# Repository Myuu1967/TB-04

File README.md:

# TB-04

自作 4bit CPU **TB-04** のプロジェクトリポジトリです。
TD4 ライクなアーキテクチャをベースに、ALU とデコーダを ROM で実装した独自設計の 4bit CPU です。
データ幅は 4bit のまま、世代ごとにアドレス空間を広げています。

TB-04 ver2 の実機。左は演算板（上）と制御板（下）を重ねたもの、右は IF 板、右端はクロック供給ユニット clock4096。

回路図・PCB（KiCAD）とプログラム・ツール類を、世代ごとのディレクトリにまとめています。回路図は KiCAD がなくても見られるよう PDF も置いています（各 README からリンク）。

## 世代

| 世代 | アドレス | 状態 | 主な特徴 | ディレクトリ |
|---|---|---|---|---|
| **ver1** | 4bit（16語） | 完成（2026-06） | 16命令・レジスタ R0〜R3・基板1枚 | [`ver1/`](ver1/) |
| **ver2** | 8bit（256語） | 完成（2026-10） | 2語命令・34命令・レジスタ R0〜R7・RAM とスタック・基板3枚・7セグ表示17台 | [`ver2/`](ver2/) |
| ver3 | 12bit（予定） | 構想中 | ポインタ・間接アドレッシング | — |

いずれも 1命令＝4クロック（ディレイスロットなし）で動きます。
各世代の仕様・ファイル構成・使い方は、それぞれのディレクトリの README を参照してください。

## 周辺機器

周辺ユニットは [`peripherals/`](peripherals/) に置いています。7segIF は ver1・ver2 のどちらでも使え、clock4096 は ver2 用です。

| ユニット | 内容 |
|---|---|
| [`7segIF`](peripherals/7segIF/) | 4bit を `0`〜`F` の7セグメントで表示するユニット（CH32V003）。ver2 では17台を使用 |
| [`clock4096`](peripherals/clock4096/) | ver2 用のクロック供給ユニット（RC 発振 4096Hz ＋ 分周、ロータリースイッチで周波数を選択）。ユニバーサル基板で製作・回路図（KiCAD・PDF）を公開 |

## ディレクトリ構成

```
ver1/         アドレス 4bit 版（回路図・PCB・アセンブラ・シミュレータ・サンプルプログラム・Pico 簡易ロジックアナライザ）
ver2/         アドレス 8bit 版（回路図・PCB・シミュレータ・ROM 生成ツール・高速ロジックアナライザ）
peripherals/  周辺ユニット（7segIF＝ver1・ver2 共通／clock4096＝ver2 用）
```

KiCAD のバージョンは、ver1 が 9.0（ロジックアナライザのみ 10.0）、ver2・7segIF・clock4096 が 10.0 です。

## 資料

- 展示会の配布資料「これまでに製作した自作CPUについてのまとめ」（2026-08-08・PDF）: <https://drive.google.com/file/d/16cySft4IG1u6tpTtqwmJSpbO6KQHhh4Z/view?usp=drive_link>
  CPU のしくみの解説と、TB-01（1bit）・TB-02（2bit）・TD4・TB-04 ver1 の構成と命令表をまとめたものです。

## ライセンス

[MIT License](LICENSE)（回路図・PCB・プログラム・ドキュメントを含む）。
ただし 7segIF の回路図・基板（`peripherals/7segIF/hardware/`）は、CC BY-SA 4.0 の作品をもとにしているため CC BY-SA 4.0 です（[`peripherals/7segIF/LICENSE`](peripherals/7segIF/LICENSE)）。

## 関連記事

ver1
- 設計編「【TB-04】4bitCPUの設計」: <https://tanuki-bayashin.hatenablog.com/entry/2026/05/27/140048>
- 完成編「【TB-04】4bitCPUの完成（アドレス4bitバージョン）」: <https://tanuki-bayashin.hatenablog.com/entry/2026/06/20/164917>
- ソースコード編「【TB-04】4bitCPUのソースコード編（シリーズ完結）」: <https://tanuki-bayashin.hatenablog.com/entry/2026/06/25/220134>
- ロジックアナライザー編「ラズベリーパイPicoによる簡易ロジックアナライザー」: <https://tanuki-bayashin.hatenablog.com/entry/2026/06/28/074330>

ver2
- 設計編「【TB-04】4bitCPUの設計（addr 8bit ver）」: <https://tanuki-bayashin.hatenablog.com/entry/2026/11/03/164404>
- 回路図とPCB設計編「【TB-04】4bitCPUの回路図とPCB設計(addr 8bit ver)」: <https://tanuki-bayashin.hatenablog.com/entry/2026/11/05/082909>
- 完成編「【TB-04】4bitCPUの完成（addr 8bit ver）」: <https://tanuki-bayashin.hatenablog.com/entry/2026/11/07/110004>
- デモ動画: <https://www.youtube.com/watch?v=xa86bRDYqcg>

周辺機器
- 「【TB-04用】7SEG表示装置（16進）の製作」: <https://tanuki-bayashin.hatenablog.com/entry/2026/08/18/172152>

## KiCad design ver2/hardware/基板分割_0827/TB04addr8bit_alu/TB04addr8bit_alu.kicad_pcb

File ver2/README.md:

# TB-04 ver2（アドレス 8bit 版）

TB-04 の2世代目です。データは 4bit のまま、アドレスを 8bit（256語）に広げ、RAM とスタックを加えました。
12bit アドレスの ver3 へ向けた通過点として作り、2026年10月にテストプログラムで全命令の動作を確認しました。
リポジトリ全体の説明は [トップの README](../README.md) を参照してください。

左は演算板（上）と制御板（下）を重ねたもの、右は IF 板、右端はクロック供給ユニット [`clock4096`](../peripherals/clock4096/)。

## アーキテクチャ

| 項目 | 仕様 |
|---|---|
| データ幅 | 4bit |
| アドレス幅 | 8bit（256語） |
| 命令形式 | 固定2語（2バイト）。1語目の上位ニブルが opcode、`E`/`F` は 8bit opcode へのプレフィックス |
| 命令数 | 34命令（ロード/ストア・PUSH/POP・CALL/RET・条件分岐4種・シフト/ローテートなど） |
| 汎用レジスタ | R0〜R7 |
| フラグ | C（キャリー）、Z（ゼロ）。書き込む命令だけが更新する（クロックゲート方式） |
| ALU | ROM 実装（28C256・入力 13bit・16演算） |
| デコーダ | ROM 実装（28C256 × 3） |
| プログラム ROM | 28C256（ZIF ソケット） |
| RAM・スタック | 6116 1個を共用。スタックは8段（SP は 3bit） |
| 制御タイミング | 4フェーズ（FCH1 → FCH2 → DCR → EXE）、1命令＝4クロック |
| 表示 | 7セグメント表示ユニット [7segIF](../peripherals/7segIF/) を17台直挿し（命令・MD・PC・OUT・IN など）＋ LED |

### メモリマップ

| アドレス | 用途 |
|---|---|
| `0x00`〜`0xBF` | プログラム ROM（192語＝96命令） |
| `0xC0`〜`0xEF` | RAM（データ 4bit） |
| `0xF0`〜`0xF7` | スタック（戻り番地 8bit） |
| `0xF8`〜`0xFB` | IN ポート 0〜3 |
| `0xFC`〜`0xFF` | OUT ポート 0〜3 |

## ブロック図

（PNG 版: [`tb04_ver2_block.png`](tb04_ver2_block.png)。図は `tools/gen_block_diagram.py` で生成）

### ブロックと主な IC

| 基板 | ブロック | 主な IC |
|---|---|---|
| IF 板 | クロック・リセット（水晶は不使用・外付け clock4096 からクロックを入れる） | 74HC14 ＋ clock4096（74HC04・4040） |
| IF 板 | IN ポート ×4 | 74HC244 ×4 |
| IF 板 | OUT ポート ×4 | 74HC377 ×4 |
| 制御板 | 位相発生（FCH1 / FCH2 / DCR / EXE） | 74HC161・74HC238 |
| 制御板 | 命令 ROM（ZIF・16バンク） | 28C256 |
| 制御板 | 命令レジスタ（byte1・byte2） | 74HC273 ×2 |
| 制御板 | デコーダ ROM ＋ 制御ラッチ | 28C256 ×2・74HC273 ×2 |
| 制御板 | PC ＋ 分岐先 MUX | 74HC161 ×2・74HC157 ×2 |
| 制御板 | SP（3bit） | 74HC193 |
| 制御板 | アドレス源の選択（mAddr / PC / SP / I-O）と IN・OUT ポートの選択 | 74HC244 ×4・74HC138・74HC157・74HC139 |
| 制御板 | 領域デコード・ゲート群 | 74HC08 ×2・74HC00 ×2・74HCT10・74HC32・74AHC04 |
| 制御板 | RAM ＋ スタック | 6116 |
| 制御板 | Y ラッチ・Y ドライバ（MD への書き出し） | 74HC273・74HC244 ×2 |
| 制御板 | Ri アドレス選択 | 74HC157 |
| 演算板 | レジスタ R0〜R7（書込先の選択を含む） | 74HC161 ×8・74HC138 |
| 演算板 | 読出し MUX（a ポート・b ポート） | 74HC253 ×8 |
| 演算板 | ALU 入力 MUX（a・b） | 74HC253 ×4 |
| 演算板 | ALU ROM | 28C256 |
| 演算板 | フラグ C / Z | 74HC74 |
| 演算板 | デコーダ ROM（ALU 用）＋ ラッチ | 28C256・74HC273 |

IC 68個の型式ごとの説明と、参照番号ごとの使い方は [`IC_LIST.md`](IC_LIST.md) にまとめています。

## 命令セット

1命令＝2語（byte1・byte2）。byte1 の上位ニブルが opcode で、`1110`（E系）・`1111`（F系）のときは下位ニブルまで含めた 8bit が opcode になります。
ビット配置の記号は `iii`=Ri、`jjj`=Rj、`mmmm`=即値、`aaaa aaaa`=番地、`pp`=ポート番号。

| 群 | 命令 | オペランド | byte1 | byte2 | 動作 | Z | C | ALU |
|---|---|---|---|---|---|:-:|:-:|---|
| 単独ニブル | NOP | - | `0000 0000` | `0000 0000` | 何もしない | - | - | NOP |
| 単独ニブル | MOV | Ri,Rj | `0001 0000` | `0iii 0jjj` | Ri←Rj | - | - | PASS_B |
| 単独ニブル | MOVI | Ri,Im4 | `0010 mmmm` | `0iii 0000` | Ri←Im4 | - | - | PASS_A |
| 単独ニブル | LD | Ri,[Im8] | `0011 0iii` | `aaaa aaaa` | Ri←MEM[Im8] | - | - | PASS_B |
| 単独ニブル | ST | [Im8],Ri | `0100 0iii` | `aaaa aaaa` | MEM[Im8]←Ri | - | - | PASS_A |
| 単独ニブル | STI | [Im8],Im4 | `0101 mmmm` | `aaaa aaaa` | MEM[Im8]←Im4 | - | - | PASS_A |
| 単独ニブル | （予約） | - | `0110/0111/1000` | — | ver3（12bitアドレス化）拡張用に温存（3枠） | - | - | - |
| E系 | JMP | Addr | `1110 0000` | `aaaa aaaa` | PC←Addr | - | - | - |
| E系 | JC | Addr | `1110 0001` | `aaaa aaaa` | C==1でPC←Addr | - | - | - |
| E系 | JNC | Addr | `1110 0010` | `aaaa aaaa` | C==0でPC←Addr | - | - | - |
| E系 | JZ | Addr | `1110 0011` | `aaaa aaaa` | Z==1でPC←Addr | - | - | - |
| E系 | JNZ | Addr | `1110 0100` | `aaaa aaaa` | Z==0でPC←Addr | - | - | - |
| E系 | CALL | Addr | `1110 0101` | `aaaa aaaa` | MEM[SP]←PC; PC←Addr; SP-- | - | - | - |
| E系 | RET | - | `1110 0110` | `0000 0000` | SP++; PC←MEM[SP] | - | - | - |
| 擬似 | HALT | - | — | — | PC←自番地（JMP $ に展開）。opcode 1110 0111 は予約 | - | - | - |
| E系 | PUSH | Ri | `1110 1000` | `0iii 0000` | MEM[SP]←Ri; SP-- | - | - | PASS_A |
| E系 | POP | Ri | `1110 1001` | `0iii 0000` | SP++; Ri←MEM[SP] | - | - | PASS_B |
| E系 | IN | Ri,port | `1110 1010` | `0iii 00pp` | Ri←IN[port] | ○ | - | PASS_B |
| E系 | OUT | port,Ri | `1110 1011` | `0iii 00pp` | OUT[port]←Ri | - | - | PASS_A |
| E系 | OUTI | port,Im4 | `1110 1100` | `00pp mmmm` | OUT[port]←Im4 | - | - | PASS_A |
| F系 | CP | Ri,Rj | `1111 0000` | `0iii 0jjj` | Ri−Rj（フラグのみ） | ○ | ○ | SUB |
| F系 | AND | Ri,Rj | `1111 0001` | `0iii 0jjj` | Ri←Ri&Rj | ○ | - | AND |
| F系 | OR | Ri,Rj | `1111 0010` | `0iii 0jjj` | Ri←Ri\|Rj | ○ | - | OR |
| F系 | XOR | Ri,Rj | `1111 0011` | `0iii 0jjj` | Ri←Ri^Rj | ○ | - | XOR |
| F系 | NOT | Ri | `1111 0100` | `0iii 0000` | Ri←!Ri | ○ | - | NOT |
| F系 | SHL | Ri | `1111 0101` | `0iii 0000` | [C,Ri]←[Ri,0] | ○ | ○ | SHL |
| F系 | SHR | Ri | `1111 0110` | `0iii 0000` | [Ri,C]←[0,Ri] | ○ | ○ | SHR |
| F系 | ROL | Ri | `1111 0111` | `0iii 0000` | Ri←{Ri[2:0],Ri[3]} | - | - | ROL |
| F系 | ROR | Ri | `1111 1000` | `0iii 0000` | Ri←{Ri[0],Ri[3:1]} | - | - | ROR |
| F系 | ADD | Ri,Rj | `1111 1001` | `0iii 0jjj` | [C,Ri]←Ri+Rj+Cin | ○ | ○ | ADD |
| F系 | ADDI | Ri,Im | `1111 1010` | `0iii mmmm` | [C,Ri]←Ri+Im+Cin | ○ | ○ | ADD |
| F系 | SUB | Ri,Rj | `1111 1011` | `0iii 0jjj` | [C,Ri]←Ri−Rj−1+Cin | ○ | ○ | SUB |
| F系 | SUBI | Ri,Im | `1111 1100` | `0iii mmmm` | [C,Ri]←Ri−Im−1+Cin | ○ | ○ | SUB |
| F系 | CLC | - | `1111 1101` | `0000 0000` | C←0 | - | ○ | CLC(14) |
| F系 | SEC | - | `1111 1110` | `0000 0000` | C←1 | - | ○ | SEC(15) |
| F系 | （予約） | - | `1111 1111` | — | 将来用に予約 | - | - | - |

- Z・C の `○` はその命令でフラグを更新、`-` は保持します。`Cin` は現在の C です（`ADD`・`SUB` の前に `CLC`／`SEC` で整えます）
- `LD`・`ST` だけは Ri を byte1 に持ちます
- 先頭ニブルが `6`〜`D` の未定義命令は NOP として動きます

## ALU コード

ALU は ROM（入力 13bit＝a 4bit・b 4bit・コード 4bit・Cin）で、結果 y と Cout・Z（＝y==0）を出します。
フラグに採用するかどうかは、命令ごとにデコーダが決めます（上の表の Z・C 列）。

| コード | 名前 | y | Cout |
|:-:|---|---|---|
| 0 | NOP | 0 | 0 |
| 1 | PASS_A | a | 0 |
| 2 | PASS_B | b | 0 |
| 3 | AND | a & b | 0 |
| 4 | OR | a \| b | 0 |
| 5 | XOR | a ^ b | 0 |
| 6 | NOT | ~a | 0 |
| 7 | SHL | {a[2:0], 0} | a[3] |
| 8 | SHR | {0, a[3:1]} | a[0] |
| 9 | ROL | {a[2:0], a[3]} | 0 |
| 10 | ROR | {a[0], a[3:1]} | 0 |
| 11 | ADD | a + b + Cin | 桁上げ |
| 12 | SUB | a − b − 1 + Cin | 0＝借り |
| 13 | （予約） | 0 | 0 |
| 14 | CLC | 0 | 0 |
| 15 | SEC | 0 | 1 |

## ディレクトリ

```
ver2/
  hardware/
    基板分割_0827/    実際に製作した3枚の基板（回路図・PCB）
      TB04addr8bit_if/     IF 板（クロック・リセット・入出力）
      TB04addr8bit_ctrl/   制御板
      TB04addr8bit_alu/    演算板
    footprints/       カスタムフットプリント
  sim/                Python による CPU モデル・アセンブラ・デモプログラム・テスト
  tools/              ROM データ生成ツール（ALU / デコーダ / ブリングアップ用テスト ROM）と生成済み ROM
  ver2_decoder_truthtable.csv   デコーダ ROM の真理値表（gen_decoder_rom.py の入力）
  pico_codes/         Pico PIO 高速ロジックアナライザ（8ns 分解能）・音と光デモの Pico 側
  IC_LIST.md          IC 68個の型式ごとの説明と使い方
  tb04_ver2_block.svg / .png   ブロック図（tools/gen_block_diagram.py で生成）
  tb04_ver2.jpg       実機の写真
```

KiCAD は 10.0 で作成しています（9.0 では開けません）。

KiCAD がなくても見られるように、回路図の PDF を置いています（KiCAD 10.0 から出力）。

- IF 板: [`TB04addr8bit_if.pdf`](hardware/基板分割_0827/TB04addr8bit_if/TB04addr8bit_if.pdf)（4ページ）
- 制御板: [`TB04addr8bit_ctrl.pdf`](hardware/基板分割_0827/TB04addr8bit_ctrl/TB04addr8bit_ctrl.pdf)（10ページ）
- 演算板: [`TB04addr8bit_alu.pdf`](hardware/基板分割_0827/TB04addr8bit_alu/TB04addr8bit_alu.pdf)（6ページ）

PDF も回路図ファイルと同じく、下の「回路図と実機の違い」にある変更は反映していません。

`hardware/TB04addr8bit_copy/` は、3枚に分割する前の1枚の回路図です（分割作業の元にした版で、その後の基板側の修正は反映していません）。

3枚の基板はケーブル（40ピン＋40ピン＋20ピン）で IF 板－制御板－演算板の順につなぎます。**20ピンのケーブルは 180°ひねって挿します。**

## 回路図と実機の違い

公開している回路図・PCB に対して、実機では次の点を変えています（回路図には反映していません）。

- **クロック**：IF 板の水晶発振（32.768kHz＋74HC4060）は、周波数が安定しなかったため使っていません。代わりに外付けのクロック供給ユニット [`clock4096`](../peripherals/clock4096/) からクロックを入れています。IF 板の手動クロックの信号をユニットへ回し、ユニットのスライドスイッチで切り替えた出力を IF 板の `CLK_CPU` につないでいます。
- **RAM の書込パルス**：CALL でスタックに誤って書き込む不具合の対策として、制御板の `U1509` の 9 番ピンを浮かせ、パッドとの間に 1kΩ を直列に入れ、9 番ピンと GND の間に 220pF をつないでいます（クロックを約 150ns 遅らせる）。経緯は完成編の記事を参照してください。
- **部品**：`U1509` は 74HC10 の代わりに 74HCT10 を使っています（入手性のため。理由は [`IC_LIST.md`](IC_LIST.md#74hct10)）。IF 板の 4060（`U502`）は、外付けクロックと出力が競合しないよう抜いています。

## シミュレータと ROM 生成ツール

Python 3 の標準ライブラリだけで動きます。

```
cd ver2/sim
python test_cpu.py                     # 全命令のテスト
python sim.py --prog counter --trace   # 1命令ごとに PC・SP・R0〜R3・C/Z・OUT を表示
python cpu_phase.py --prog countdown   # 4フェーズ（FCH1/FCH2/DCR/EXE）単位で実行
```

デモ（`--prog`）は ver1 から移植した `counter`・`led_flow`・`fibonacci`・`ramen_timer`・`kakezan`・`life_ca`・`pred_prey` と、ver2 用の `calc`・`sec_count`・`showcase`（展示デモ）・`hanoi`・`ishitori`・`kaprekar`・`rule_ca`・`collatz`・`calc_normal`・`calc_rpn`・`ecosystem`・`melody` です。プログラムは `programs.py` に Python のコードで書いています（各デモの説明は関数の docstring）。

`cpu.py`（命令単位）は、命令の実行結果（レジスタ・フラグ・RAM・OUT）が実機と一致します（テスト ROM の期待値をこのモデルで求め、実機は全バンク合格）。実機との違いは次のとおりです。

- リセット直後の C/Z・OUT・RAM を 0 にしています（実機では不定）。
- `cpu_phase.py` は POP/RET の SP 更新などを EXE にまとめており、フェーズ単位では実機と異なるところがあります。
- ns 単位のタイミング（ゲート遅延やヒゲ）は扱いません。

```
cd ver2/tools
python gen_alu_rom.py       # alu_rom.bin / .hex（ALU ROM U603）
python gen_decoder_rom.py   # decoder_romA/B/C.bin / .hex（デコーダ ROM U704/U703/U706）
python gen_test_rom.py      # test_rom.bin / .hex（命令 ROM U604 用・16バンク）
python gen_test_rom.py --demo   # demo_rom.bin / .hex（展示用デモ ROM・16バンク）
```

テスト ROM は 1バンク＝256バイトで、制御板のロータリースイッチ `SW601` の位置がバンク番号になります。バンク 0〜14 は命令を依存順に1グループずつ確かめるテスト、バンク 15 は展示デモ（`showcase`）です。

デモ ROM のバンクは次のとおりです（シミュレータで確認済み・実機は確認中）。

| バンク | デモ | バンク | デモ |
|---|---|---|---|
| 0 | showcase（単語→10進4桁カウンタ） | 8 | ishitori（石取り・CPU は必勝法） |
| 1 | counter | 9 | kaprekar（カプレカ数 6174） |
| 2 | led_flow | 10 | rule_ca（16セルの Rule90/30） |
| 3 | fibonacci | 11 | collatz（3n+1・16bit） |
| 4 | life_ca | 12 | calc_normal（ふつうの計算機） |
| 5 | pred_prey | 13 | calc_rpn（逆ポーランド記法の計算機） |
| 6 | kakezan | 14 | ecosystem（生態系ゲーム） |
| 7 | hanoi（ハノイの塔4枚・再帰） | 15 | melody（音と光・Pico が音源） |

入力は 16キーのキーパッドだけです（MM74C922：キーコード 0〜F→IN0、押下（DA）→IN1 の bit0）。DIP は全部 OFF にしておきます（DIP は直列抵抗なしで VDD につながるため）。おもな操作は、石取り＝1/2/3 で取る・F で新ゲーム、カプレカ＝数字4桁→A〜F で開始、Rule CA＝9 で Rule90・3 で Rule30、コラッツ＝押すたびに右から1桁入れてやり直す、生態系＝1 で草を植える・2 で狩る・0 で最初から、です。counter・led_flow・life_ca は起動時に IN0 を読むので、キーを押してからリセットします（MM74C922 は最後のキーのコードを保持する）。

## 高速ロジックアナライザ

ブリングアップで見つかった CALL のスタック誤書込（RAM の書込パルスと PC の変化の競合、数十 ns）を測るために作りました。使い方は [`pico_codes/README.md`](pico_codes/README.md) を参照してください。

## 関連記事

- 設計編「【TB-04】4bitCPUの設計（addr 8bit ver）」: <https://tanuki-bayashin.hatenablog.com/entry/2026/11/03/164404>
- 回路図とPCB設計編「【TB-04】4bitCPUの回路図とPCB設計(addr 8bit ver)」: <https://tanuki-bayashin.hatenablog.com/entry/2026/11/05/082909>
- 完成編「【TB-04】4bitCPUの完成（addr 8bit ver）」: <https://tanuki-bayashin.hatenablog.com/entry/2026/11/07/110004>
- 番外編「使ったIC」: <https://tanuki-bayashin.hatenablog.com/entry/2026/11/08/191106>
- デモ動画: <https://www.youtube.com/watch?v=xa86bRDYqcg>

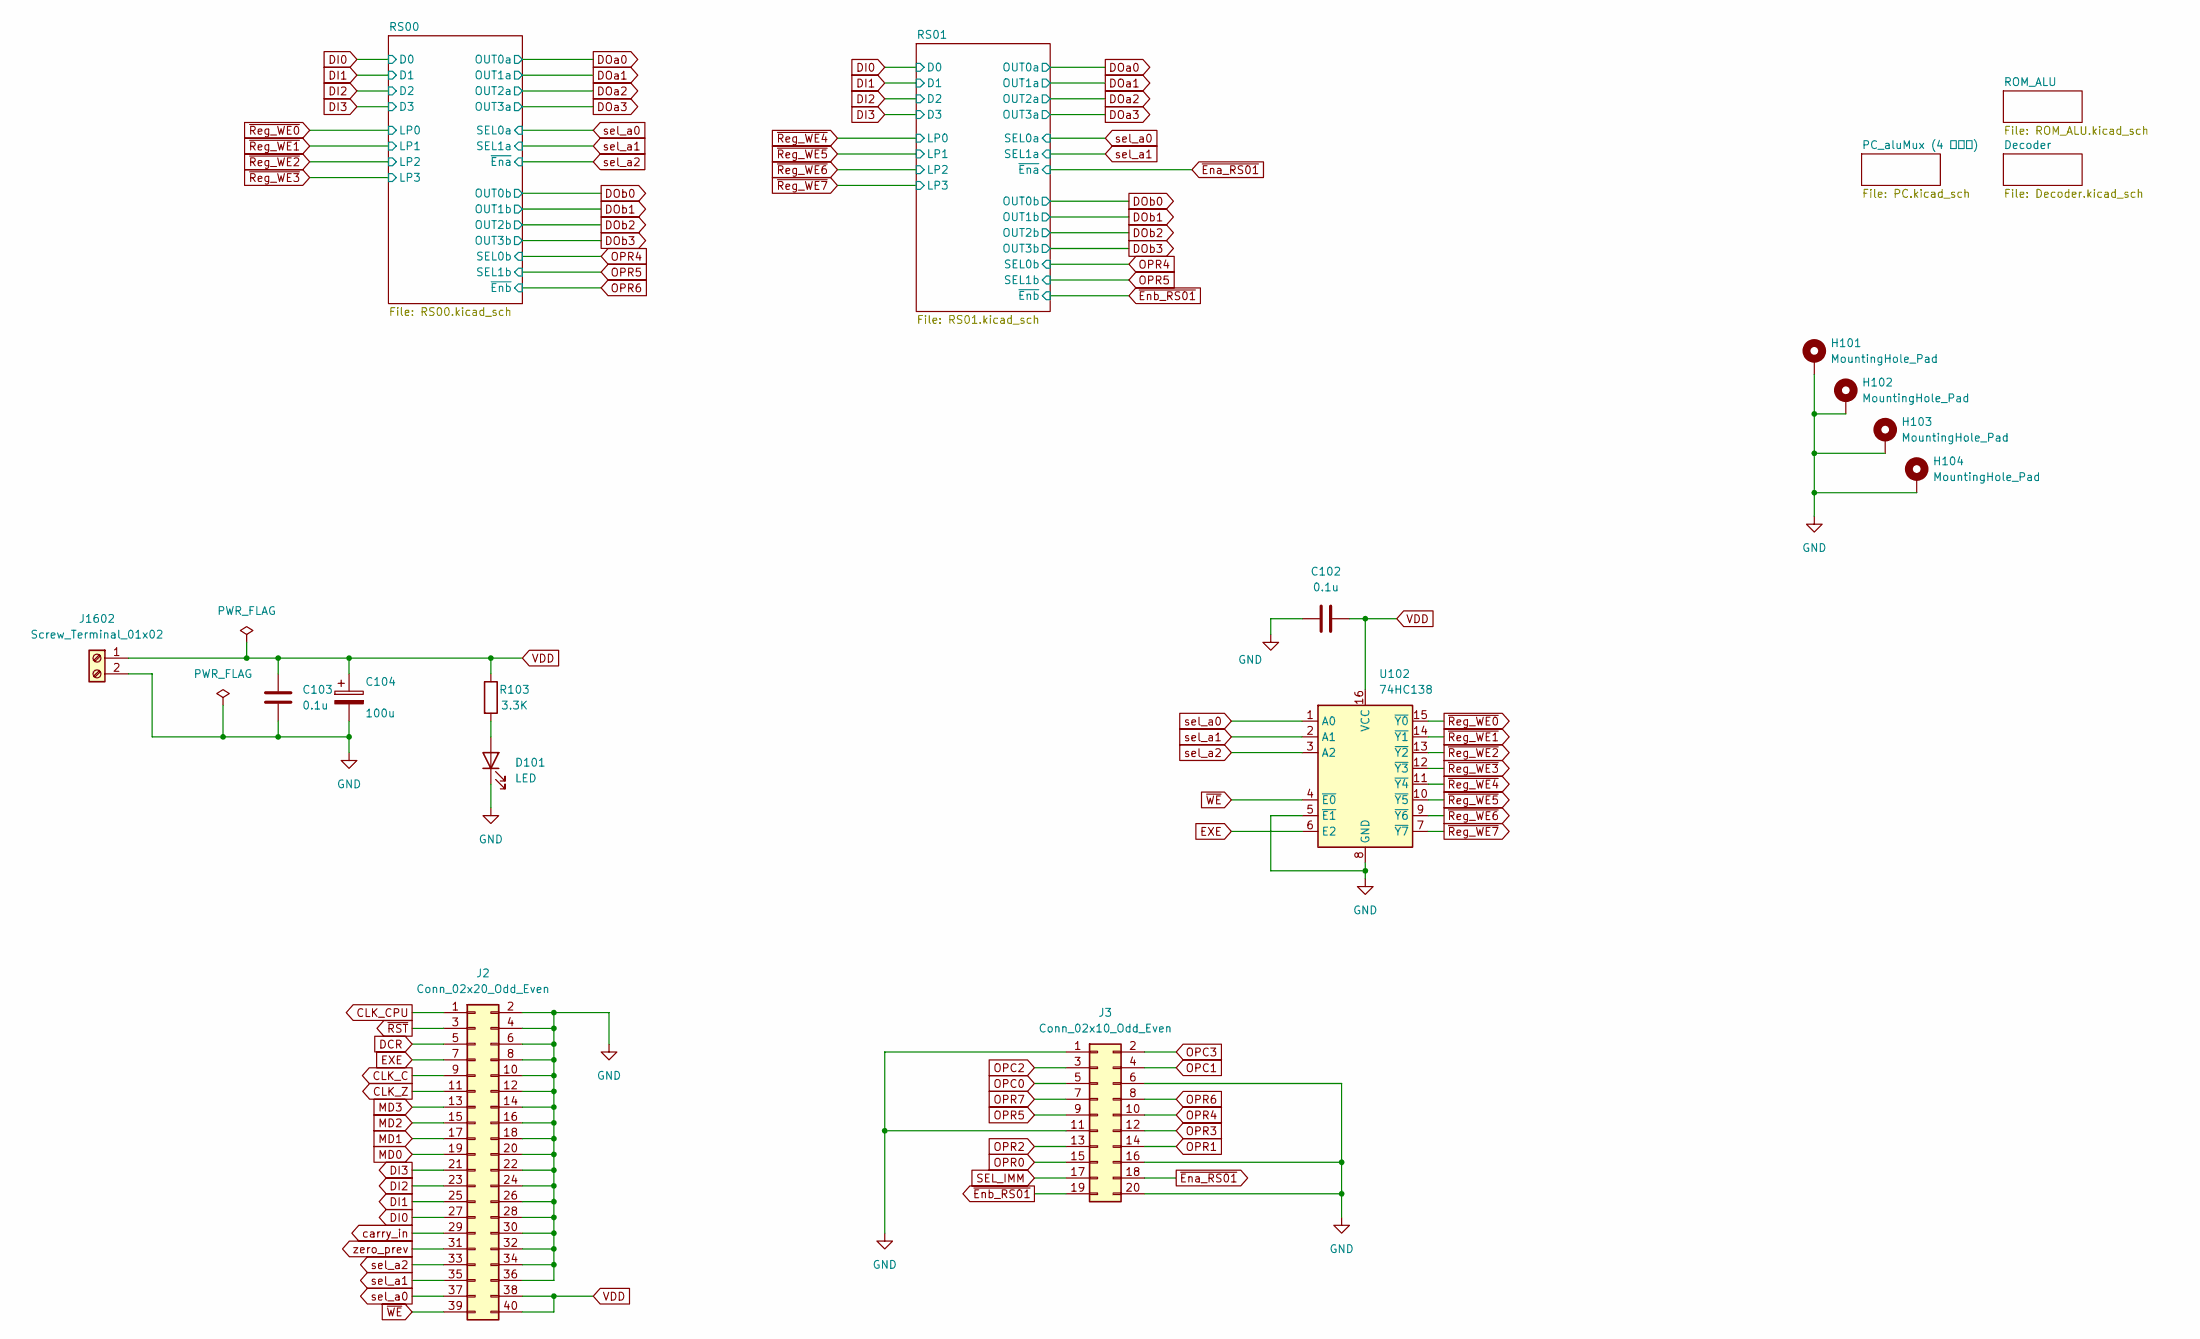
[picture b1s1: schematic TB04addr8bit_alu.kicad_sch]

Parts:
C102, C103: 0.1u; C_Disc_D4.3mm_W1.9mm_P5.00mm
C104: 100u; CP_Radial_D5.0mm_P2.00mm
D101: LED; LED_D3.0mm_Clear
H101, H102, H103, H104: MountingHole_Pad; MountingHole_3.2mm_M3_Pad_Via
J2: Conn_02x20_Odd_Even; PinSocket_2x20_P2.54mm_Vertical
J3: Conn_02x10_Odd_Even; PinSocket_2x10_P2.54mm_Vertical
J1602: Screw_Terminal_01x02; TerminalBlock_MaiXu_MX126-5.0-02P_1x02_P5.00mm
R103: 3.3K; R_Axial_DIN0207_L6.3mm_D2.5mm_P7.62mm_Horizontal
U102: 74HC138; DIP-16_W7.62mm_Socket

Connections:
CLK_C: J2.9; also elsewhere on the board
CLK_CPU: J2.1; also elsewhere on the board
CLK_Z: J2.11; also elsewhere on the board
DCR: J2.5; also elsewhere on the board
DI0: J2.27; also elsewhere on the board
DI1: J2.25; also elsewhere on the board
DI2: J2.23; also elsewhere on the board
DI3: J2.21; also elsewhere on the board
EXE: J2.7, U102.6 (E2)
GND: C102.2, C103.2, C104.2, D101.1 (K), H101.1 (1_1), H102.1 (1_1), H103.1 (1_1), H104.1 (1_1), J2.2, J2.4, J2.6, J2.8, J2.10, J2.12, J2.14, J2.16, J2.18, J2.20, J2.22, J2.24, J2.26, J2.28, J2.30, J2.32, J2.34, J2.36, J3.1, J3.6, J3.11, J3.16, J3.20, J1602.2, U102.5 (~E1), U102.8 (GND); also elsewhere on the board
MD0: J2.19; also elsewhere on the board
MD1: J2.17; also elsewhere on the board
MD2: J2.15; also elsewhere on the board
MD3: J2.13; also elsewhere on the board
unnamed: D101.2 (A), R103.2
OPC0: J3.5; also elsewhere on the board
OPC1: J3.4; also elsewhere on the board
OPC2: J3.3; also elsewhere on the board
OPC3: J3.2; also elsewhere on the board
OPR0: J3.15; also elsewhere on the board
OPR1: J3.14; also elsewhere on the board
OPR2: J3.13; also elsewhere on the board
OPR3: J3.12; also elsewhere on the board
OPR4: J3.10; also elsewhere on the board
OPR5: J3.9; also elsewhere on the board
OPR6: J3.8; also elsewhere on the board
OPR7: J3.7; also elsewhere on the board
SEL_IMM: J3.17; also elsewhere on the board
VDD: C102.1, C103.1, C104.1, J2.38, J2.40, J1602.1, R103.1, U102.16 (VCC); also elsewhere on the board
carry_in: J2.29; also elsewhere on the board
sel_a0: J2.37, U102.1 (A0); also elsewhere on the board
sel_a1: J2.35, U102.2 (A1); also elsewhere on the board
sel_a2: J2.33, U102.3 (A2); also elsewhere on the board
zero_prev: J2.31; also elsewhere on the board
~Ena_RS01: J3.18; also elsewhere on the board
~Enb_RS01: J3.19; also elsewhere on the board
~RST: J2.3; also elsewhere on the board
~Reg_WE0: U102.15 (~Y0); also elsewhere on the board
~Reg_WE1: U102.14 (~Y1); also elsewhere on the board
~Reg_WE2: U102.13 (~Y2); also elsewhere on the board
~Reg_WE3: U102.12 (~Y3); also elsewhere on the board
~Reg_WE4: U102.11 (~Y4); also elsewhere on the board
~Reg_WE5: U102.10 (~Y5); also elsewhere on the board
~Reg_WE6: U102.9 (~Y6); also elsewhere on the board
~Reg_WE7: U102.7 (~Y7); also elsewhere on the board
~WE: J2.39, U102.4 (~E0)

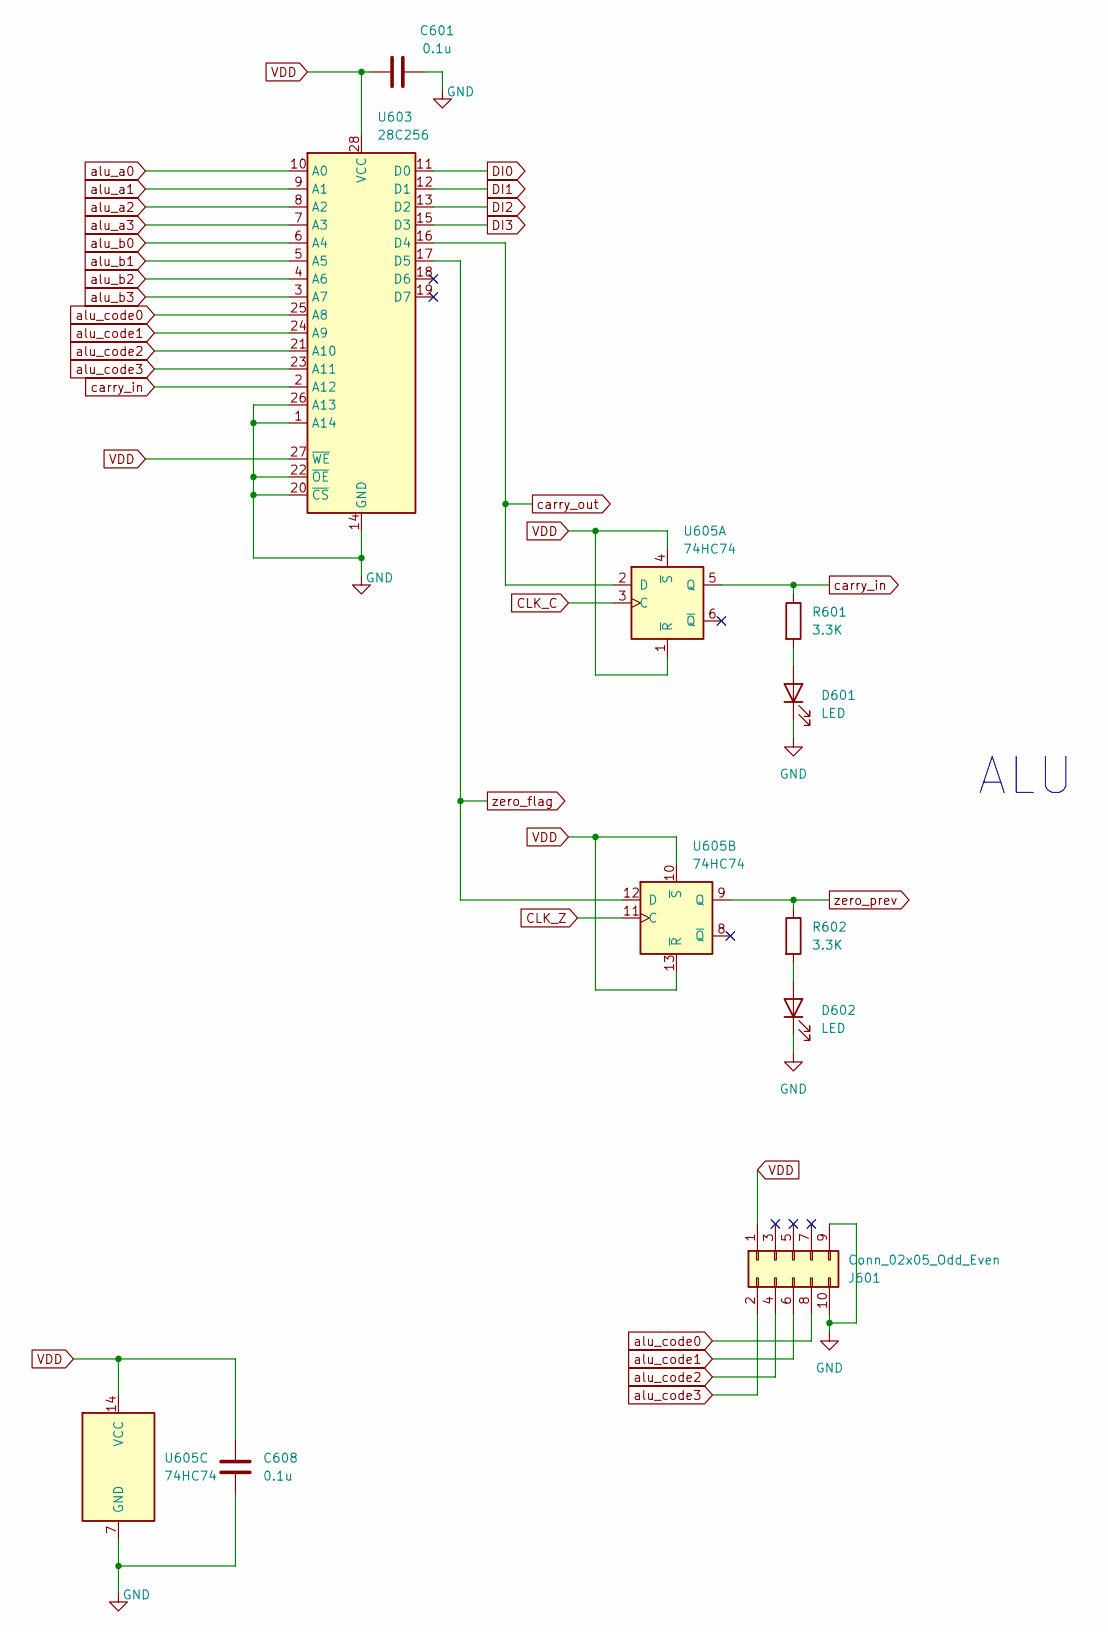
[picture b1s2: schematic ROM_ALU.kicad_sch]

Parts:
C601, C608: 0.1u; C_Disc_D4.3mm_W1.9mm_P5.00mm
D601, D602: LED; LED_D3.0mm_Clear
J601: Conn_02x05_Odd_Even; PinSocket_2x05_P2.54mm_Vertical
R601, R602: 3.3K; R_Axial_DIN0207_L6.3mm_D2.5mm_P7.62mm_Horizontal
U603: 28C256; DIP-28_W15.24mm_Socket
U605: 74HC74; DIP-14_W7.62mm_Socket

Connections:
CLK_C: U605.3 (C); also elsewhere on the board
CLK_Z: U605.11 (C); also elsewhere on the board
DI0: U603.11 (D0); also elsewhere on the board
DI1: U603.12 (D1); also elsewhere on the board
DI2: U603.13 (D2); also elsewhere on the board
DI3: U603.15 (D3); also elsewhere on the board
GND: C601.1, C608.2, D601.1 (K), D602.1 (K), J601.9, J601.10, U603.1 (A14), U603.14 (GND), U603.20 (~CS), U603.22 (~OE), U603.26 (A13), U605.7 (GND); also elsewhere on the board
unnamed: D601.2 (A), R601.2
unnamed: D602.2 (A), R602.2
VDD: C601.2, C608.1, J601.1, U603.27 (~WE), U603.28 (VCC), U605.1 (~R), U605.4 (~S), U605.10 (~S), U605.13 (~R), U605.14 (VCC); also elsewhere on the board
alu_a0: U603.10 (A0); also elsewhere on the board
alu_a1: U603.9 (A1); also elsewhere on the board
alu_a2: U603.8 (A2); also elsewhere on the board
alu_a3: U603.7 (A3); also elsewhere on the board
alu_b0: U603.6 (A4); also elsewhere on the board
alu_b1: U603.5 (A5); also elsewhere on the board
alu_b2: U603.4 (A6); also elsewhere on the board
alu_b3: U603.3 (A7); also elsewhere on the board
alu_code0: J601.8, U603.25 (A8); also elsewhere on the board
alu_code1: J601.6, U603.24 (A9); also elsewhere on the board
alu_code2: J601.4, U603.21 (A10); also elsewhere on the board
alu_code3: J601.2, U603.23 (A11); also elsewhere on the board
carry_in: R601.1, U603.2 (A12), U605.5 (Q); also elsewhere on the board
carry_out: U603.16 (D4), U605.2 (D)
zero_flag: U603.17 (D5), U605.12 (D)
zero_prev: R602.1, U605.9 (Q); also elsewhere on the board

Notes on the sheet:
ALU

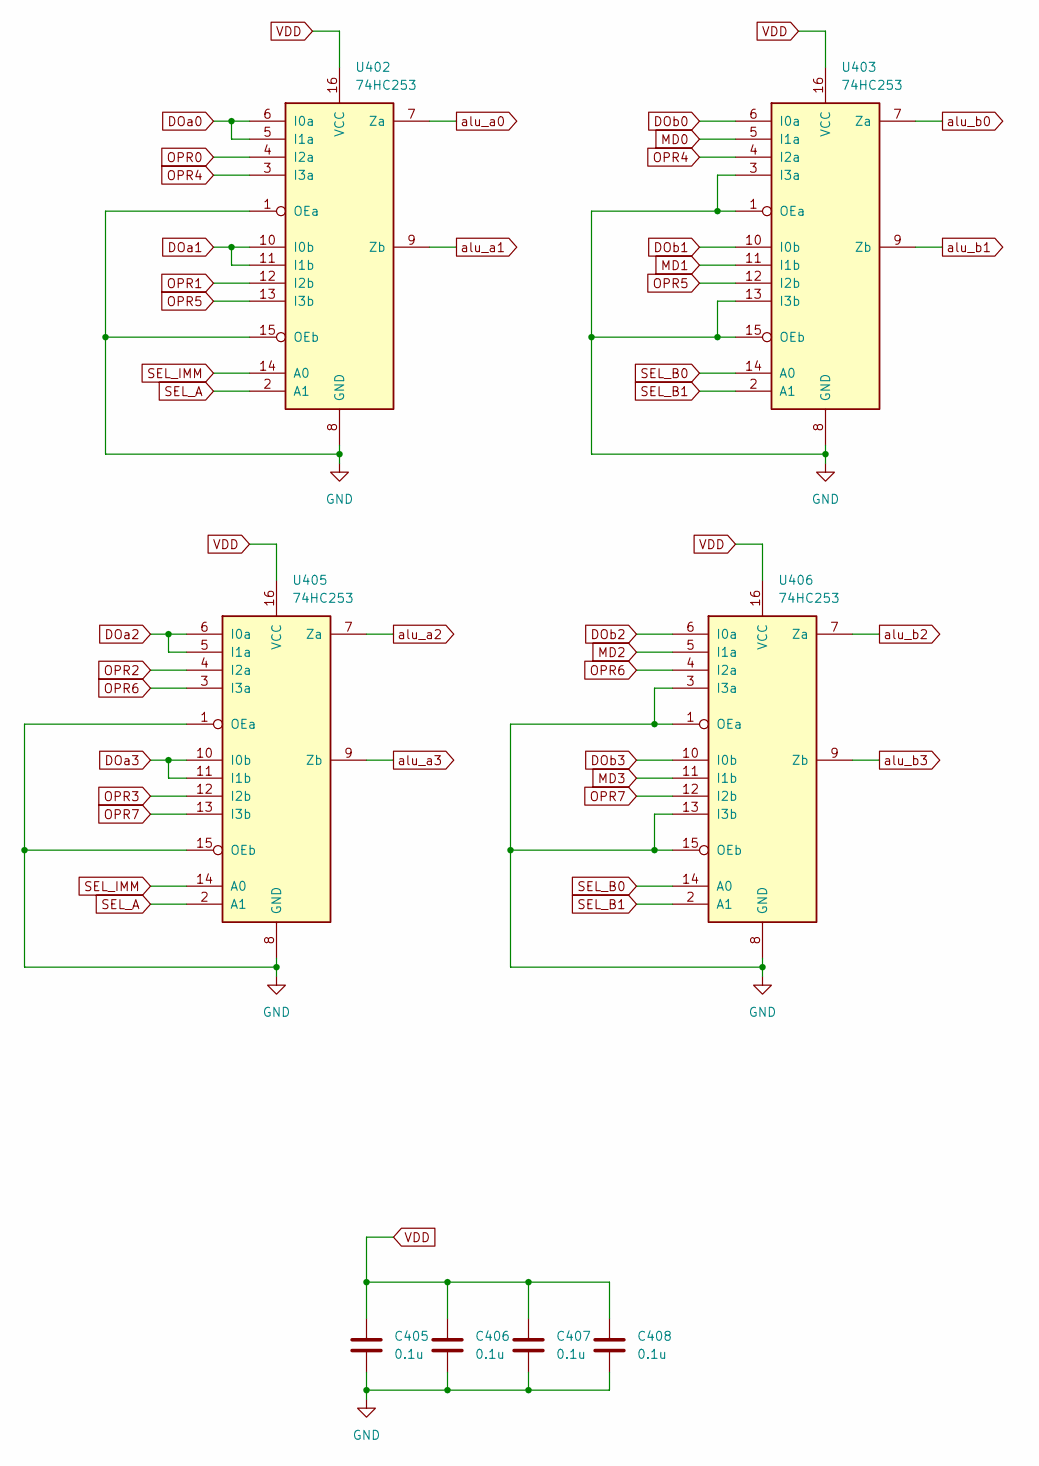
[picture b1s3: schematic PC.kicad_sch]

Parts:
C405, C406, C407, C408: 0.1u; C_Disc_D4.3mm_W1.9mm_P5.00mm
U402, U403, U405, U406: 74HC253; DIP-16_W7.62mm_Socket

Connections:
DOa0: U402.5 (I1a), U402.6 (I0a); also elsewhere on the board
DOa1: U402.10 (I0b), U402.11 (I1b); also elsewhere on the board
DOa2: U405.5 (I1a), U405.6 (I0a); also elsewhere on the board
DOa3: U405.10 (I0b), U405.11 (I1b); also elsewhere on the board
DOb0: U403.6 (I0a); also elsewhere on the board
DOb1: U403.10 (I0b); also elsewhere on the board
DOb2: U406.6 (I0a); also elsewhere on the board
DOb3: U406.10 (I0b); also elsewhere on the board
GND: C405.1, C406.1, C407.1, C408.1, U402.1 (OEa), U402.8 (GND), U402.15 (OEb), U403.1 (OEa), U403.3 (I3a), U403.8 (GND), U403.13 (I3b), U403.15 (OEb), U405.1 (OEa), U405.8 (GND), U405.15 (OEb), U406.1 (OEa), U406.3 (I3a), U406.8 (GND), U406.13 (I3b), U406.15 (OEb); also elsewhere on the board
MD0: U403.5 (I1a); also elsewhere on the board
MD1: U403.11 (I1b); also elsewhere on the board
MD2: U406.5 (I1a); also elsewhere on the board
MD3: U406.11 (I1b); also elsewhere on the board
OPR0: U402.4 (I2a); also elsewhere on the board
OPR1: U402.12 (I2b); also elsewhere on the board
OPR2: U405.4 (I2a); also elsewhere on the board
OPR3: U405.12 (I2b); also elsewhere on the board
OPR4: U402.3 (I3a), U403.4 (I2a); also elsewhere on the board
OPR5: U402.13 (I3b), U403.12 (I2b); also elsewhere on the board
OPR6: U405.3 (I3a), U406.4 (I2a); also elsewhere on the board
OPR7: U405.13 (I3b), U406.12 (I2b); also elsewhere on the board
SEL_A: U402.2 (A1), U405.2 (A1); also elsewhere on the board
SEL_B0: U403.14 (A0), U406.14 (A0); also elsewhere on the board
SEL_B1: U403.2 (A1), U406.2 (A1); also elsewhere on the board
SEL_IMM: U402.14 (A0), U405.14 (A0); also elsewhere on the board
VDD: C405.2, C406.2, C407.2, C408.2, U402.16 (VCC), U403.16 (VCC), U405.16 (VCC), U406.16 (VCC); also elsewhere on the board
alu_a0: U402.7 (Za); also elsewhere on the board
alu_a1: U402.9 (Zb); also elsewhere on the board
alu_a2: U405.7 (Za); also elsewhere on the board
alu_a3: U405.9 (Zb); also elsewhere on the board
alu_b0: U403.7 (Za); also elsewhere on the board
alu_b1: U403.9 (Zb); also elsewhere on the board
alu_b2: U406.7 (Za); also elsewhere on the board
alu_b3: U406.9 (Zb); also elsewhere on the board

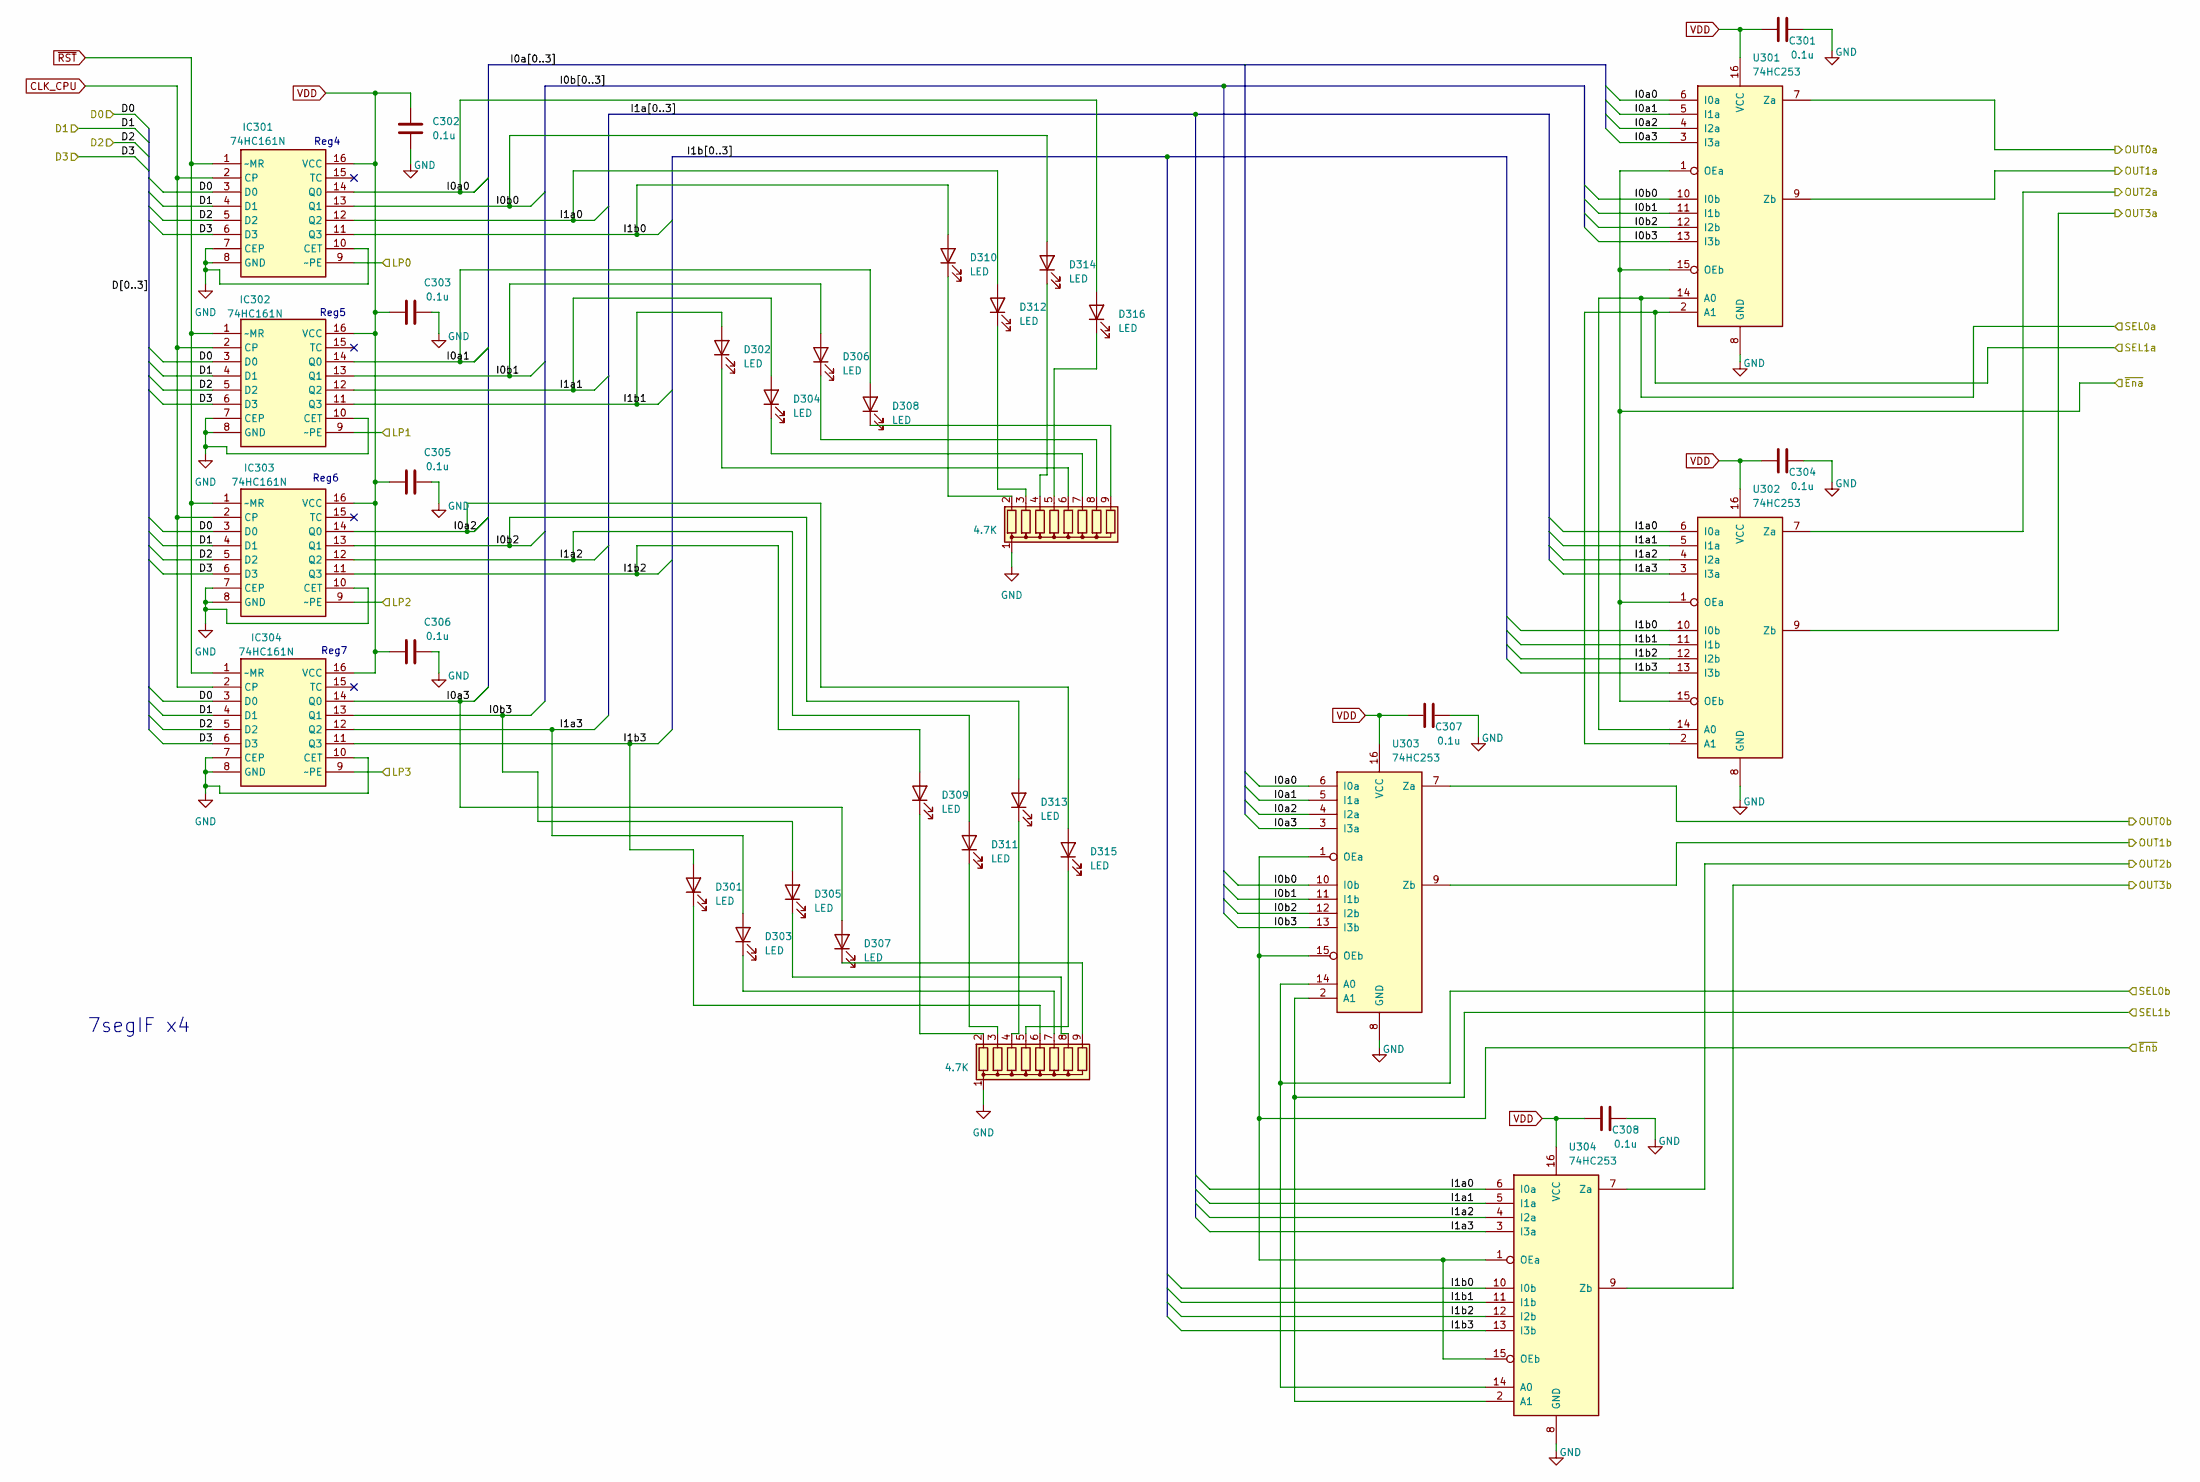
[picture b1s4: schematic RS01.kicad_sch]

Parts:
C301, C302, C303, C304, C305, C306, C307, C308: 0.1u; C_Disc_D4.3mm_W1.9mm_P5.00mm
D301, D302, D303, D304, D305, D306, D307, D308, D309, D310, D311, D312, D313, D314, D315, D316: LED; LED_D3.0mm_Clear
IC301, IC302, IC303, IC304: 74HC161N; DIP-16_W7.62mm_Socket; Manufacturer_Part_Number 74HC161N
RN301, RN302: 4.7K; R_Array_SIP9
U301, U302, U303, U304: 74HC253; DIP-16_W7.62mm_Socket

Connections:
/RS01/I0a0: D316.2 (A), IC301.14 (Q0), U301.6 (I0a), U303.6 (I0a)
/RS01/I0a1: D308.2 (A), IC302.14 (Q0), U301.5 (I1a), U303.5 (I1a)
/RS01/I0a2: D315.2 (A), IC303.14 (Q0), U301.4 (I2a), U303.4 (I2a)
/RS01/I0a3: D307.2 (A), IC304.14 (Q0), U301.3 (I3a), U303.3 (I3a)
/RS01/I0b0: D314.2 (A), IC301.13 (Q1), U301.10 (I0b), U303.10 (I0b)
/RS01/I0b1: D306.2 (A), IC302.13 (Q1), U301.11 (I1b), U303.11 (I1b)
/RS01/I0b2: D313.2 (A), IC303.13 (Q1), U301.12 (I2b), U303.12 (I2b)
/RS01/I0b3: D305.2 (A), IC304.13 (Q1), U301.13 (I3b), U303.13 (I3b)
/RS01/I1a0: D312.2 (A), IC301.12 (Q2), U302.6 (I0a), U304.6 (I0a)
/RS01/I1a1: D304.2 (A), IC302.12 (Q2), U302.5 (I1a), U304.5 (I1a)
/RS01/I1a2: D311.2 (A), IC303.12 (Q2), U302.4 (I2a), U304.4 (I2a)
/RS01/I1a3: D303.2 (A), IC304.12 (Q2), U302.3 (I3a), U304.3 (I3a)
/RS01/I1b0: D310.2 (A), IC301.11 (Q3), U302.10 (I0b), U304.10 (I0b)
/RS01/I1b1: D302.2 (A), IC302.11 (Q3), U302.11 (I1b), U304.11 (I1b)
/RS01/I1b2: D309.2 (A), IC303.11 (Q3), U302.12 (I2b), U304.12 (I2b)
/RS01/I1b3: D301.2 (A), IC304.11 (Q3), U302.13 (I3b), U304.13 (I3b)
CLK_CPU: IC301.2 (CP), IC302.2 (CP), IC303.2 (CP), IC304.2 (CP); also elsewhere on the board
DI0: IC301.3 (D0), IC302.3 (D0), IC303.3 (D0), IC304.3 (D0); also elsewhere on the board
DI1: IC301.4 (D1), IC302.4 (D1), IC303.4 (D1), IC304.4 (D1); also elsewhere on the board
DI2: IC301.5 (D2), IC302.5 (D2), IC303.5 (D2), IC304.5 (D2); also elsewhere on the board
DI3: IC301.6 (D3), IC302.6 (D3), IC303.6 (D3), IC304.6 (D3); also elsewhere on the board
DOa0: U301.7 (Za); also elsewhere on the board
DOa1: U301.9 (Zb); also elsewhere on the board
DOa2: U302.7 (Za); also elsewhere on the board
DOa3: U302.9 (Zb); also elsewhere on the board
DOb0: U303.7 (Za); also elsewhere on the board
DOb1: U303.9 (Zb); also elsewhere on the board
DOb2: U304.7 (Za); also elsewhere on the board
DOb3: U304.9 (Zb); also elsewhere on the board
GND: C301.1, C302.1, C303.1, C304.1, C305.1, C306.1, C307.1, C308.1, IC301.7 (CEP), IC301.8 (GND), IC301.10 (CET), IC302.7 (CEP), IC302.8 (GND), IC302.10 (CET), IC303.7 (CEP), IC303.8 (GND), IC303.10 (CET), IC304.7 (CEP), IC304.8 (GND), IC304.10 (CET), RN301.1 (common), RN302.1 (common), U301.8 (GND), U302.8 (GND), U303.8 (GND), U304.8 (GND); also elsewhere on the board
unnamed: D301.1 (K), RN301.6 (R5)
unnamed: D302.1 (K), RN302.6 (R5)
unnamed: D303.1 (K), RN301.7 (R6)
unnamed: D304.1 (K), RN302.7 (R6)
unnamed: D305.1 (K), RN301.8 (R7)
unnamed: D306.1 (K), RN302.8 (R7)
unnamed: D307.1 (K), RN301.9 (R8)
unnamed: D308.1 (K), RN302.9 (R8)
unnamed: D309.1 (K), RN301.2 (R1)
unnamed: D310.1 (K), RN302.2 (R1)
unnamed: D311.1 (K), RN301.3 (R2)
unnamed: D312.1 (K), RN302.3 (R2)
unnamed: D313.1 (K), RN301.4 (R3)
unnamed: D314.1 (K), RN302.4 (R3)
unnamed: D315.1 (K), RN301.5 (R4)
unnamed: D316.1 (K), RN302.5 (R4)
OPR4: U303.14 (A0), U304.14 (A0); also elsewhere on the board
OPR5: U303.2 (A1), U304.2 (A1); also elsewhere on the board
VDD: C301.2, C302.2, C303.2, C304.2, C305.2, C306.2, C307.2, C308.2, IC301.16 (VCC), IC302.16 (VCC), IC303.16 (VCC), IC304.16 (VCC), U301.16 (VCC), U302.16 (VCC), U303.16 (VCC), U304.16 (VCC); also elsewhere on the board
sel_a0: U301.14 (A0), U302.14 (A0); also elsewhere on the board
sel_a1: U301.2 (A1), U302.2 (A1); also elsewhere on the board
~Ena_RS01: U301.1 (OEa), U301.15 (OEb), U302.1 (OEa), U302.15 (OEb); also elsewhere on the board
~Enb_RS01: U303.1 (OEa), U303.15 (OEb), U304.1 (OEa), U304.15 (OEb); also elsewhere on the board
~RST: IC301.1 (~MR), IC302.1 (~MR), IC303.1 (~MR), IC304.1 (~MR); also elsewhere on the board
~Reg_WE4: IC301.9 (~PE); also elsewhere on the board
~Reg_WE5: IC302.9 (~PE); also elsewhere on the board
~Reg_WE6: IC303.9 (~PE); also elsewhere on the board
~Reg_WE7: IC304.9 (~PE); also elsewhere on the board

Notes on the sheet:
Reg5
Reg4
Reg7
7segIF x4
Reg6
